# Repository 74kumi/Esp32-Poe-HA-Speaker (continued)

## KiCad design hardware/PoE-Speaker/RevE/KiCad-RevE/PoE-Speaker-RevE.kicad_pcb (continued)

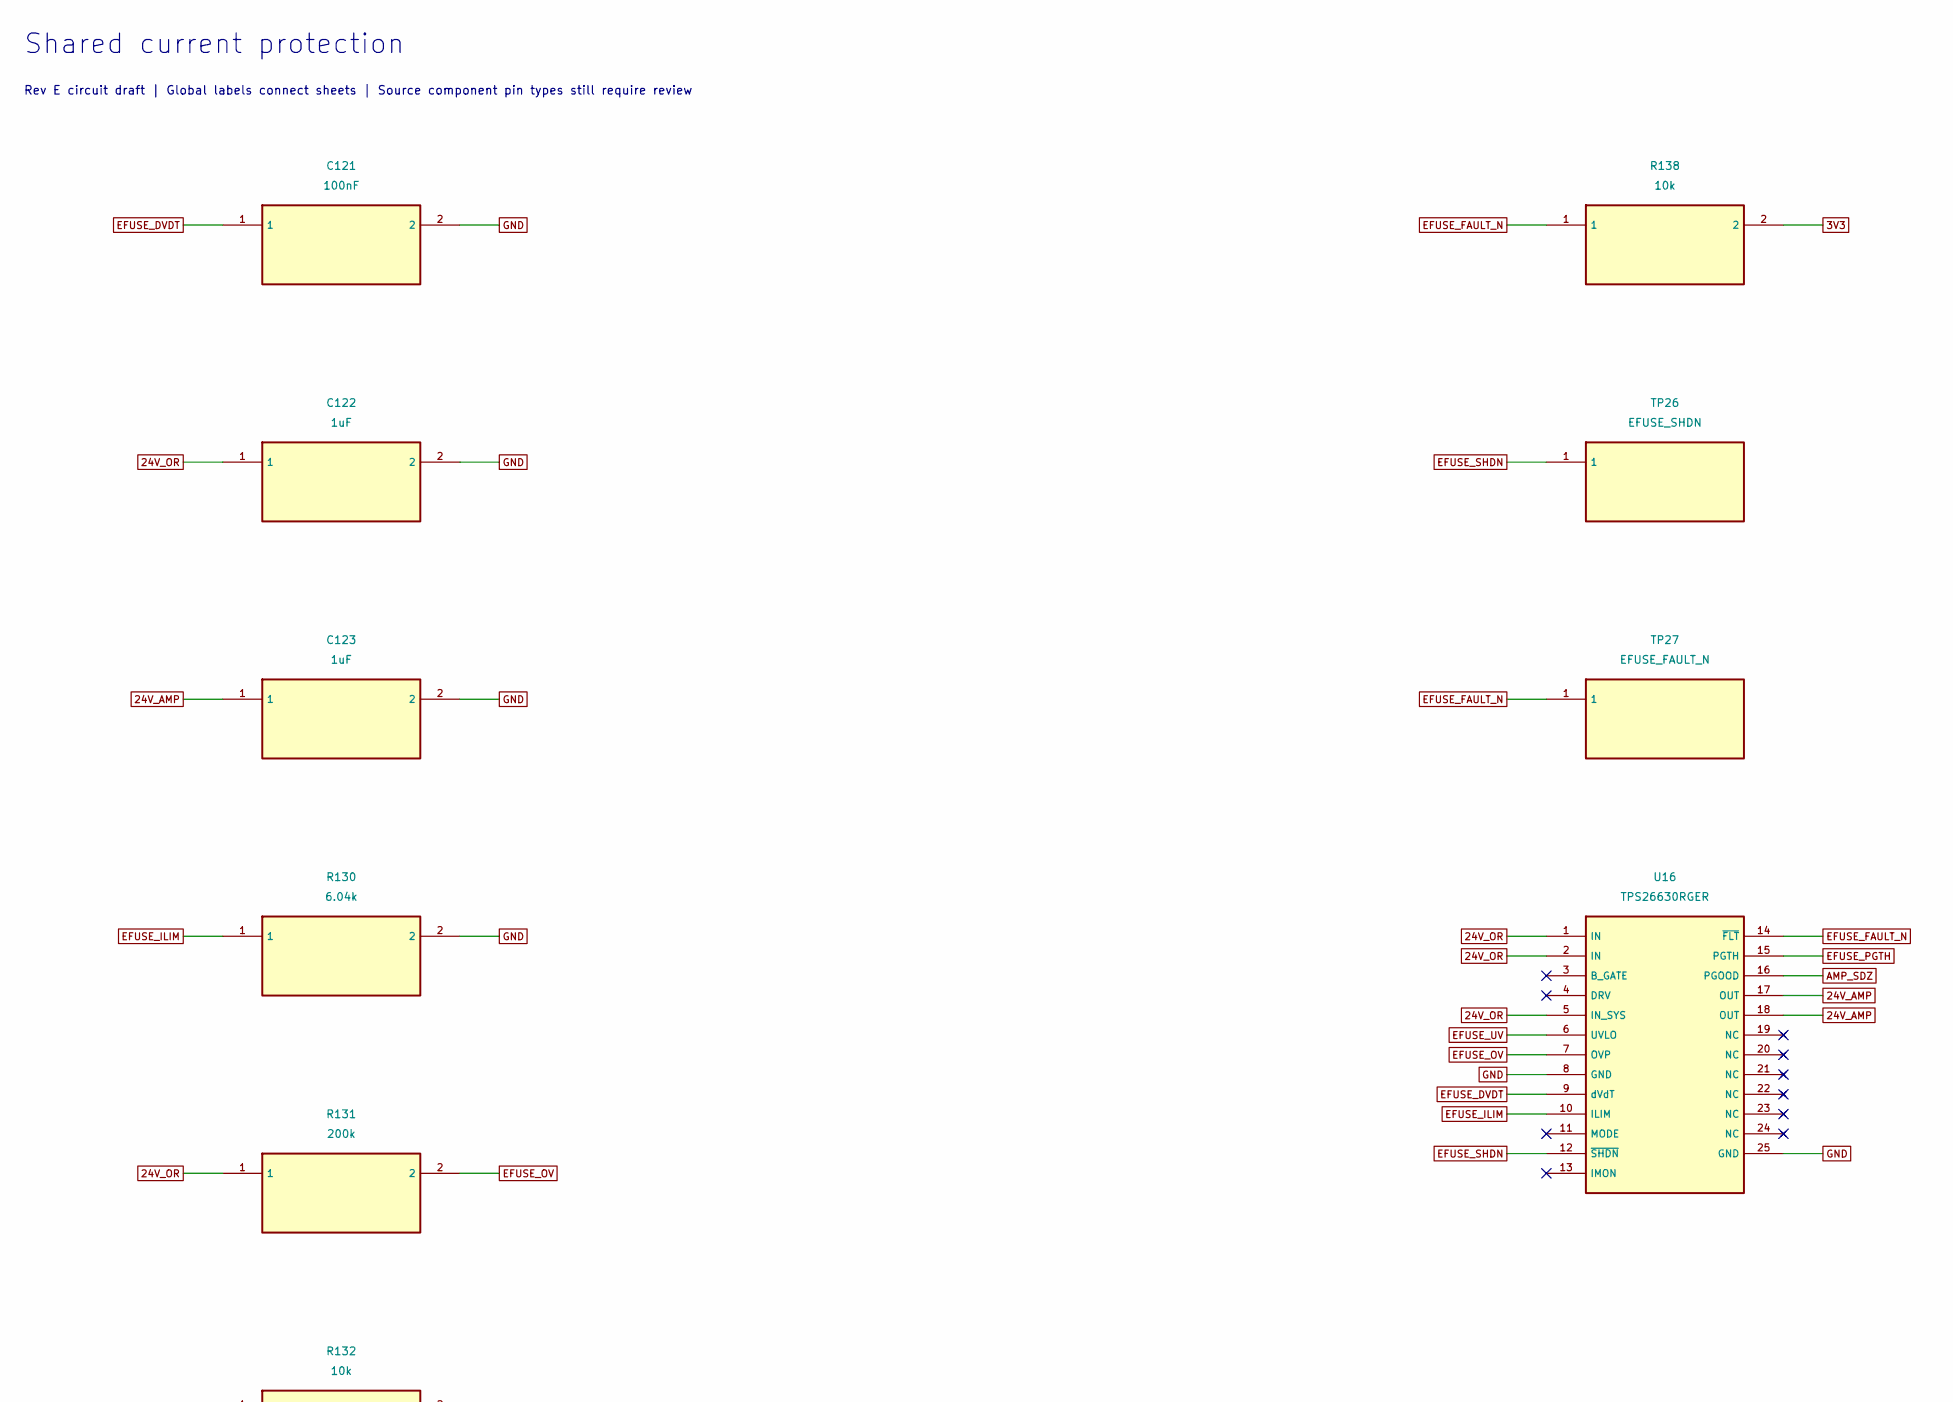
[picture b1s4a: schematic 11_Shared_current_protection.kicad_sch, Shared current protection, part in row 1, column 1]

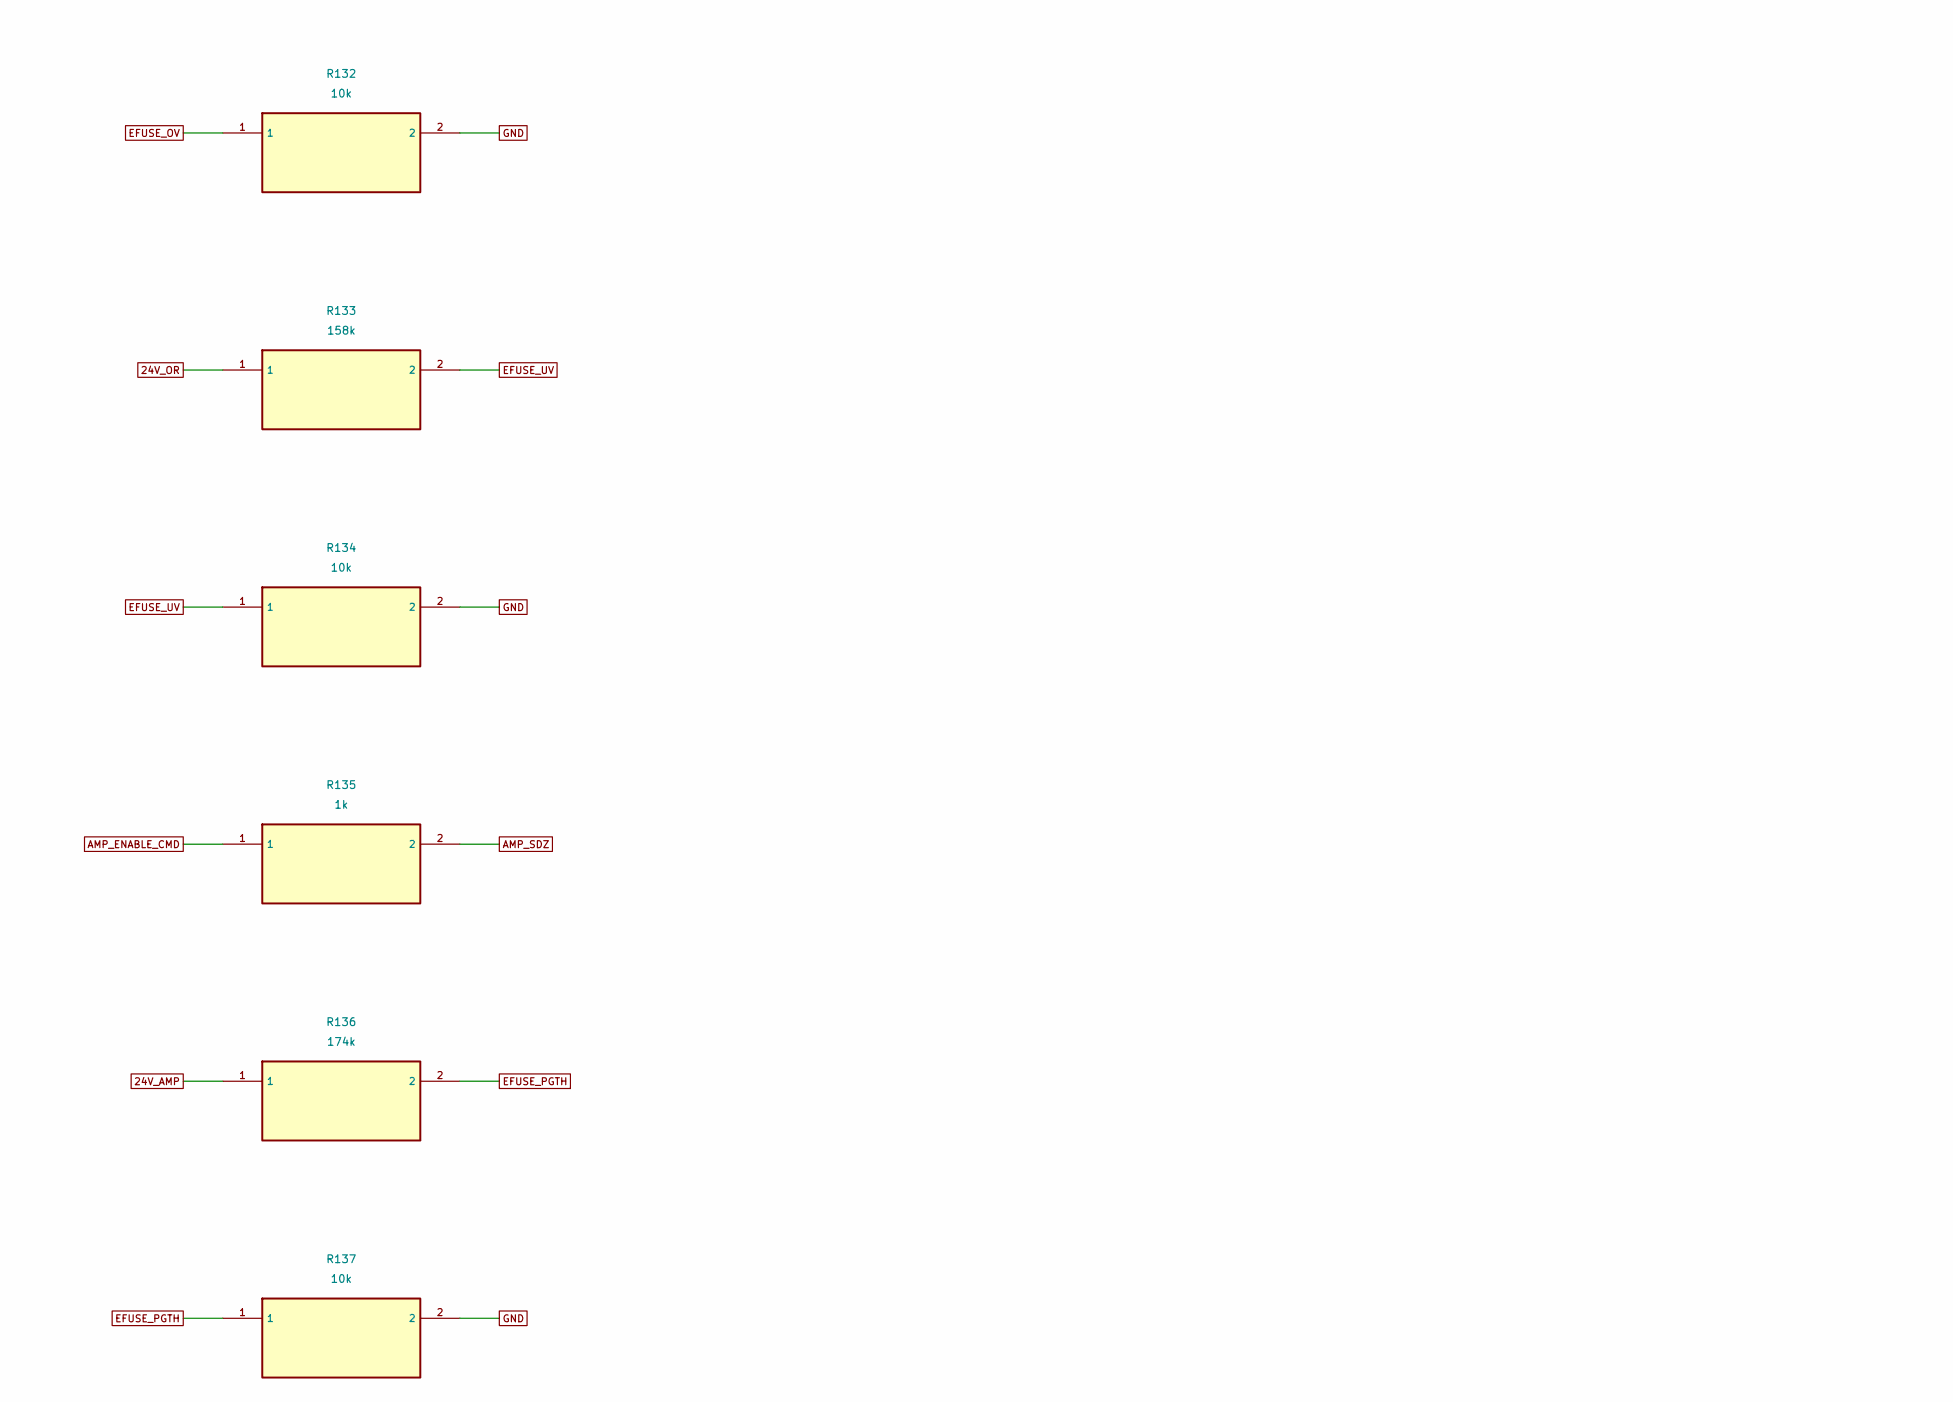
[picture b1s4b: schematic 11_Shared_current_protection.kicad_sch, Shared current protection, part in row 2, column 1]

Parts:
C121: 100nF; C_1210_3225Metric; Voltage Rating 100 V; Tolerance 5%; Manufacturer Part Number C1210C104J1GACTU
C122: 1uF; C_1210_3225Metric; Voltage Rating 100 V; Tolerance 10%; Manufacturer Part Number C1210C105K1RACTU
C123: 1uF; C123_RevB; Voltage Rating 50 V; Tolerance 10%; Manufacturer Part Number C0805C105K5RACTU
R130: 6.04k; R130_RevB; Tolerance 1%; Power rating 0.125 W conservative; Manufacturer Part Number TNPW08056K04FHEA
R131: 200k; R131_RevB; Tolerance 0.1%; Power rating 0.125 W conservative; Manufacturer Part Number TNPW0805200KBYEA
R132: 10k; R132_RevB; Tolerance 0.1%; Power rating 0.125 W conservative; Manufacturer Part Number TNPW080510K0BYEA
R133: 158k; R133_RevB; Tolerance 1%; Power rating 0.125 W conservative; Manufacturer Part Number TNPW0805158KFHEA
R134: 10k; R134_RevB; Tolerance 1%; Power rating 0.125 W conservative; Manufacturer Part Number TNPW080510K0FHEA
R135: 1k; R135_RevB; Tolerance 1%; Power rating 0.125 W conservative; Manufacturer Part Number TNPW08051K00FHEA
R136: 174k; R136_RevB; Tolerance 1%; Power rating 0.125 W conservative; Manufacturer Part Number TNPW0805174KFHEA
R137: 10k; R137_RevB; Tolerance 1%; Power rating 0.125 W conservative; Manufacturer Part Number TNPW080510K0FHEA
R138: 10k; R138_RevB; Tolerance 1%; Power rating 0.125 W conservative; Manufacturer Part Number TNPW080510K0FHEA
TP26: EFUSE_SHDN; TP26_RevB; Manufacturer Part Number TBD
TP27: EFUSE_FAULT_N; TP27_RevB; Manufacturer Part Number TBD
U16: TPS26630RGER; U16_RevB; Manufacturer Part Number TPS26630RGER

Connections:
3V3: R138.2; also elsewhere on the board
24V_AMP: C123.1, R136.1, U16.17 (OUT), U16.18 (OUT); also elsewhere on the board
24V_OR: C122.1, R131.1, R133.1, U16.1 (IN), U16.2 (IN), U16.5 (IN_SYS); also elsewhere on the board
AMP_ENABLE_CMD: R135.1; also elsewhere on the board
AMP_SDZ: R135.2, U16.16 (PGOOD); also elsewhere on the board
EFUSE_DVDT: C121.1, U16.9 (dVdT)
EFUSE_FAULT_N: R138.1, TP27.1, U16.14 (~FLT)
EFUSE_ILIM: R130.1, U16.10 (ILIM)
EFUSE_OV: R131.2, R132.1, U16.7 (OVP)
EFUSE_PGTH: R136.2, R137.1, U16.15 (PGTH)
EFUSE_SHDN: TP26.1, U16.12 (~SHDN)
EFUSE_UV: R133.2, R134.1, U16.6 (UVLO)
GND: C121.2, C122.2, C123.2, R130.2, R132.2, R134.2, R137.2, U16.8 (GND), U16.25 (GND); also elsewhere on the board

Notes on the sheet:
Rev E circuit draft | Global labels connect sheets | Source component pin types still require review
Shared current protection

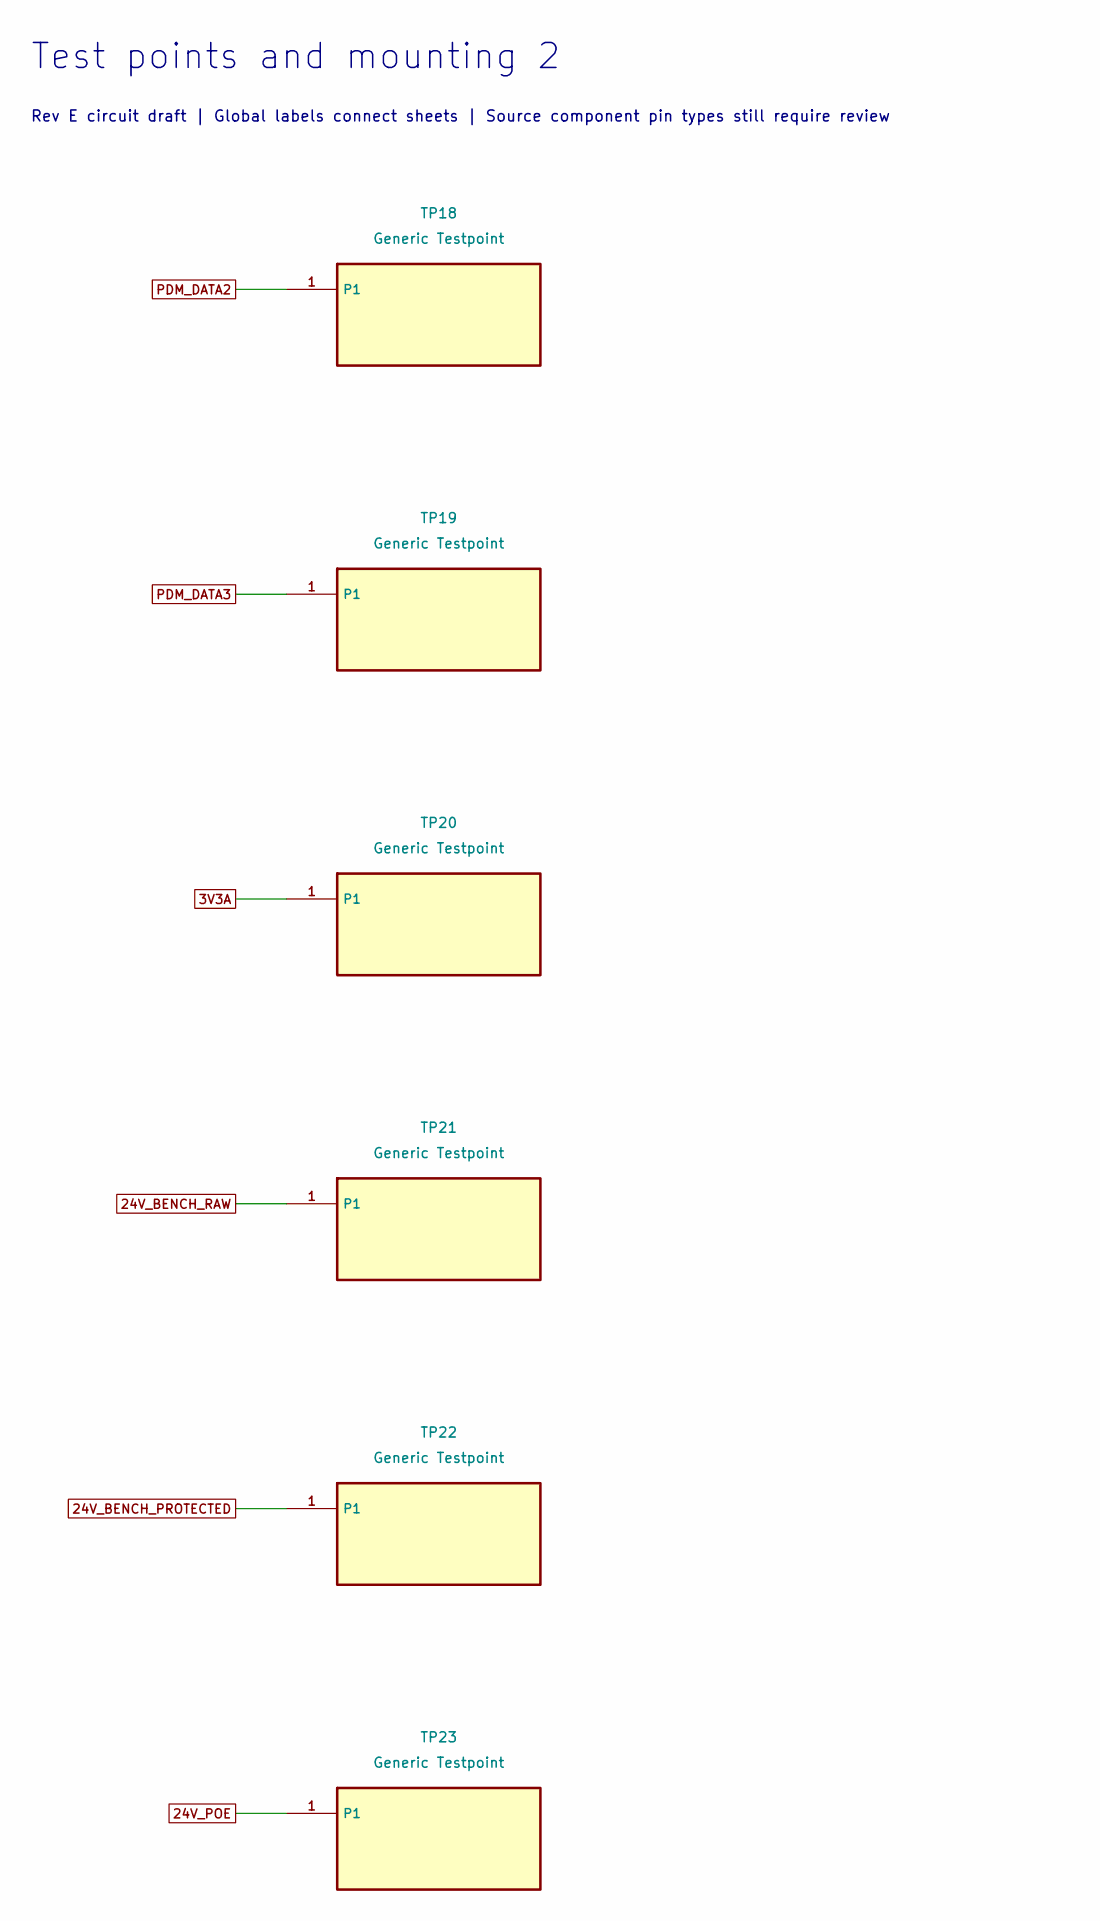
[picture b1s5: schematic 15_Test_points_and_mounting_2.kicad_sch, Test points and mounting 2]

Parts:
TP18: Generic Testpoint; TP18_RevB; Part Type Test Point
TP19: Generic Testpoint; TP19_RevB; Part Type Test Point
TP20: Generic Testpoint; TP20_RevB; Part Type Test Point
TP21: Generic Testpoint; TP21_RevB; Part Type Test Point
TP22: Generic Testpoint; TP22_RevB; Part Type Test Point
TP23: Generic Testpoint; TP23_RevB; Part Type Test Point

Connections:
3V3A: TP20.1; also elsewhere on the board
24V_BENCH_PROTECTED: TP22.1; also elsewhere on the board
24V_BENCH_RAW: TP21.1; also elsewhere on the board
24V_POE: TP23.1; also elsewhere on the board
PDM_DATA2: TP18.1; also elsewhere on the board
PDM_DATA3: TP19.1; also elsewhere on the board

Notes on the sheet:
Test points and mounting 2
Rev E circuit draft | Global labels connect sheets | Source component pin types still require review

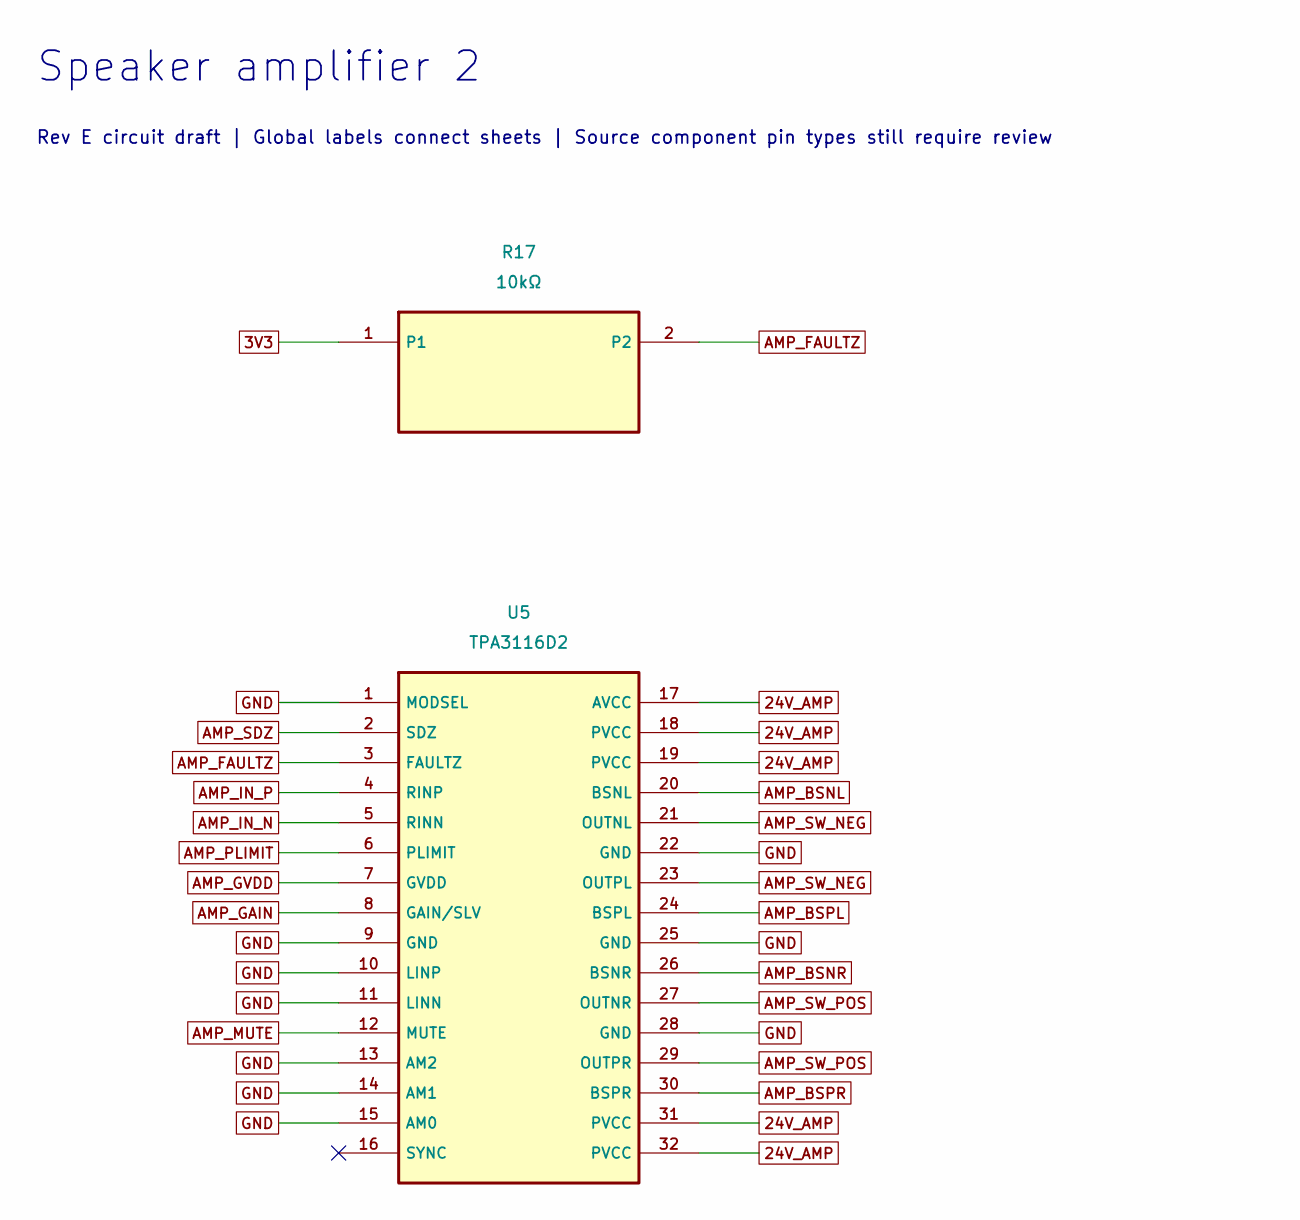
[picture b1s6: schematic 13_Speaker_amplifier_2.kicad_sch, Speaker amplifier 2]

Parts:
R17: 10kΩ; R17_RevB; Tolerance 1%; Power rating 0.10 W conservative; Part Type Resistor
U5: TPA3116D2; U5_RevB; Part Type Integrated Circuit

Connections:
3V3: R17.1; also elsewhere on the board
24V_AMP: U5.17 (AVCC), U5.18 (PVCC), U5.19 (PVCC), U5.31 (PVCC), U5.32 (PVCC); also elsewhere on the board
AMP_BSNL: U5.20 (BSNL); also elsewhere on the board
AMP_BSNR: U5.26 (BSNR); also elsewhere on the board
AMP_BSPL: U5.24 (BSPL); also elsewhere on the board
AMP_BSPR: U5.30 (BSPR); also elsewhere on the board
AMP_FAULTZ: R17.2, U5.3 (FAULTZ); also elsewhere on the board
AMP_GAIN: U5.8 (GAIN/SLV); also elsewhere on the board
AMP_GVDD: U5.7 (GVDD); also elsewhere on the board
AMP_IN_N: U5.5 (RINN); also elsewhere on the board
AMP_IN_P: U5.4 (RINP); also elsewhere on the board
AMP_MUTE: U5.12 (MUTE); also elsewhere on the board
AMP_PLIMIT: U5.6 (PLIMIT); also elsewhere on the board
AMP_SDZ: U5.2 (SDZ); also elsewhere on the board
AMP_SW_NEG: U5.21 (OUTNL), U5.23 (OUTPL); also elsewhere on the board
AMP_SW_POS: U5.27 (OUTNR), U5.29 (OUTPR); also elsewhere on the board
GND: U5.1 (MODSEL), U5.9 (GND), U5.10 (LINP), U5.11 (LINN), U5.13 (AM2), U5.14 (AM1), U5.15 (AM0), U5.22 (GND), U5.25 (GND), U5.28 (GND); also elsewhere on the board

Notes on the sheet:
Speaker amplifier 2
Rev E circuit draft | Global labels connect sheets | Source component pin types still require review

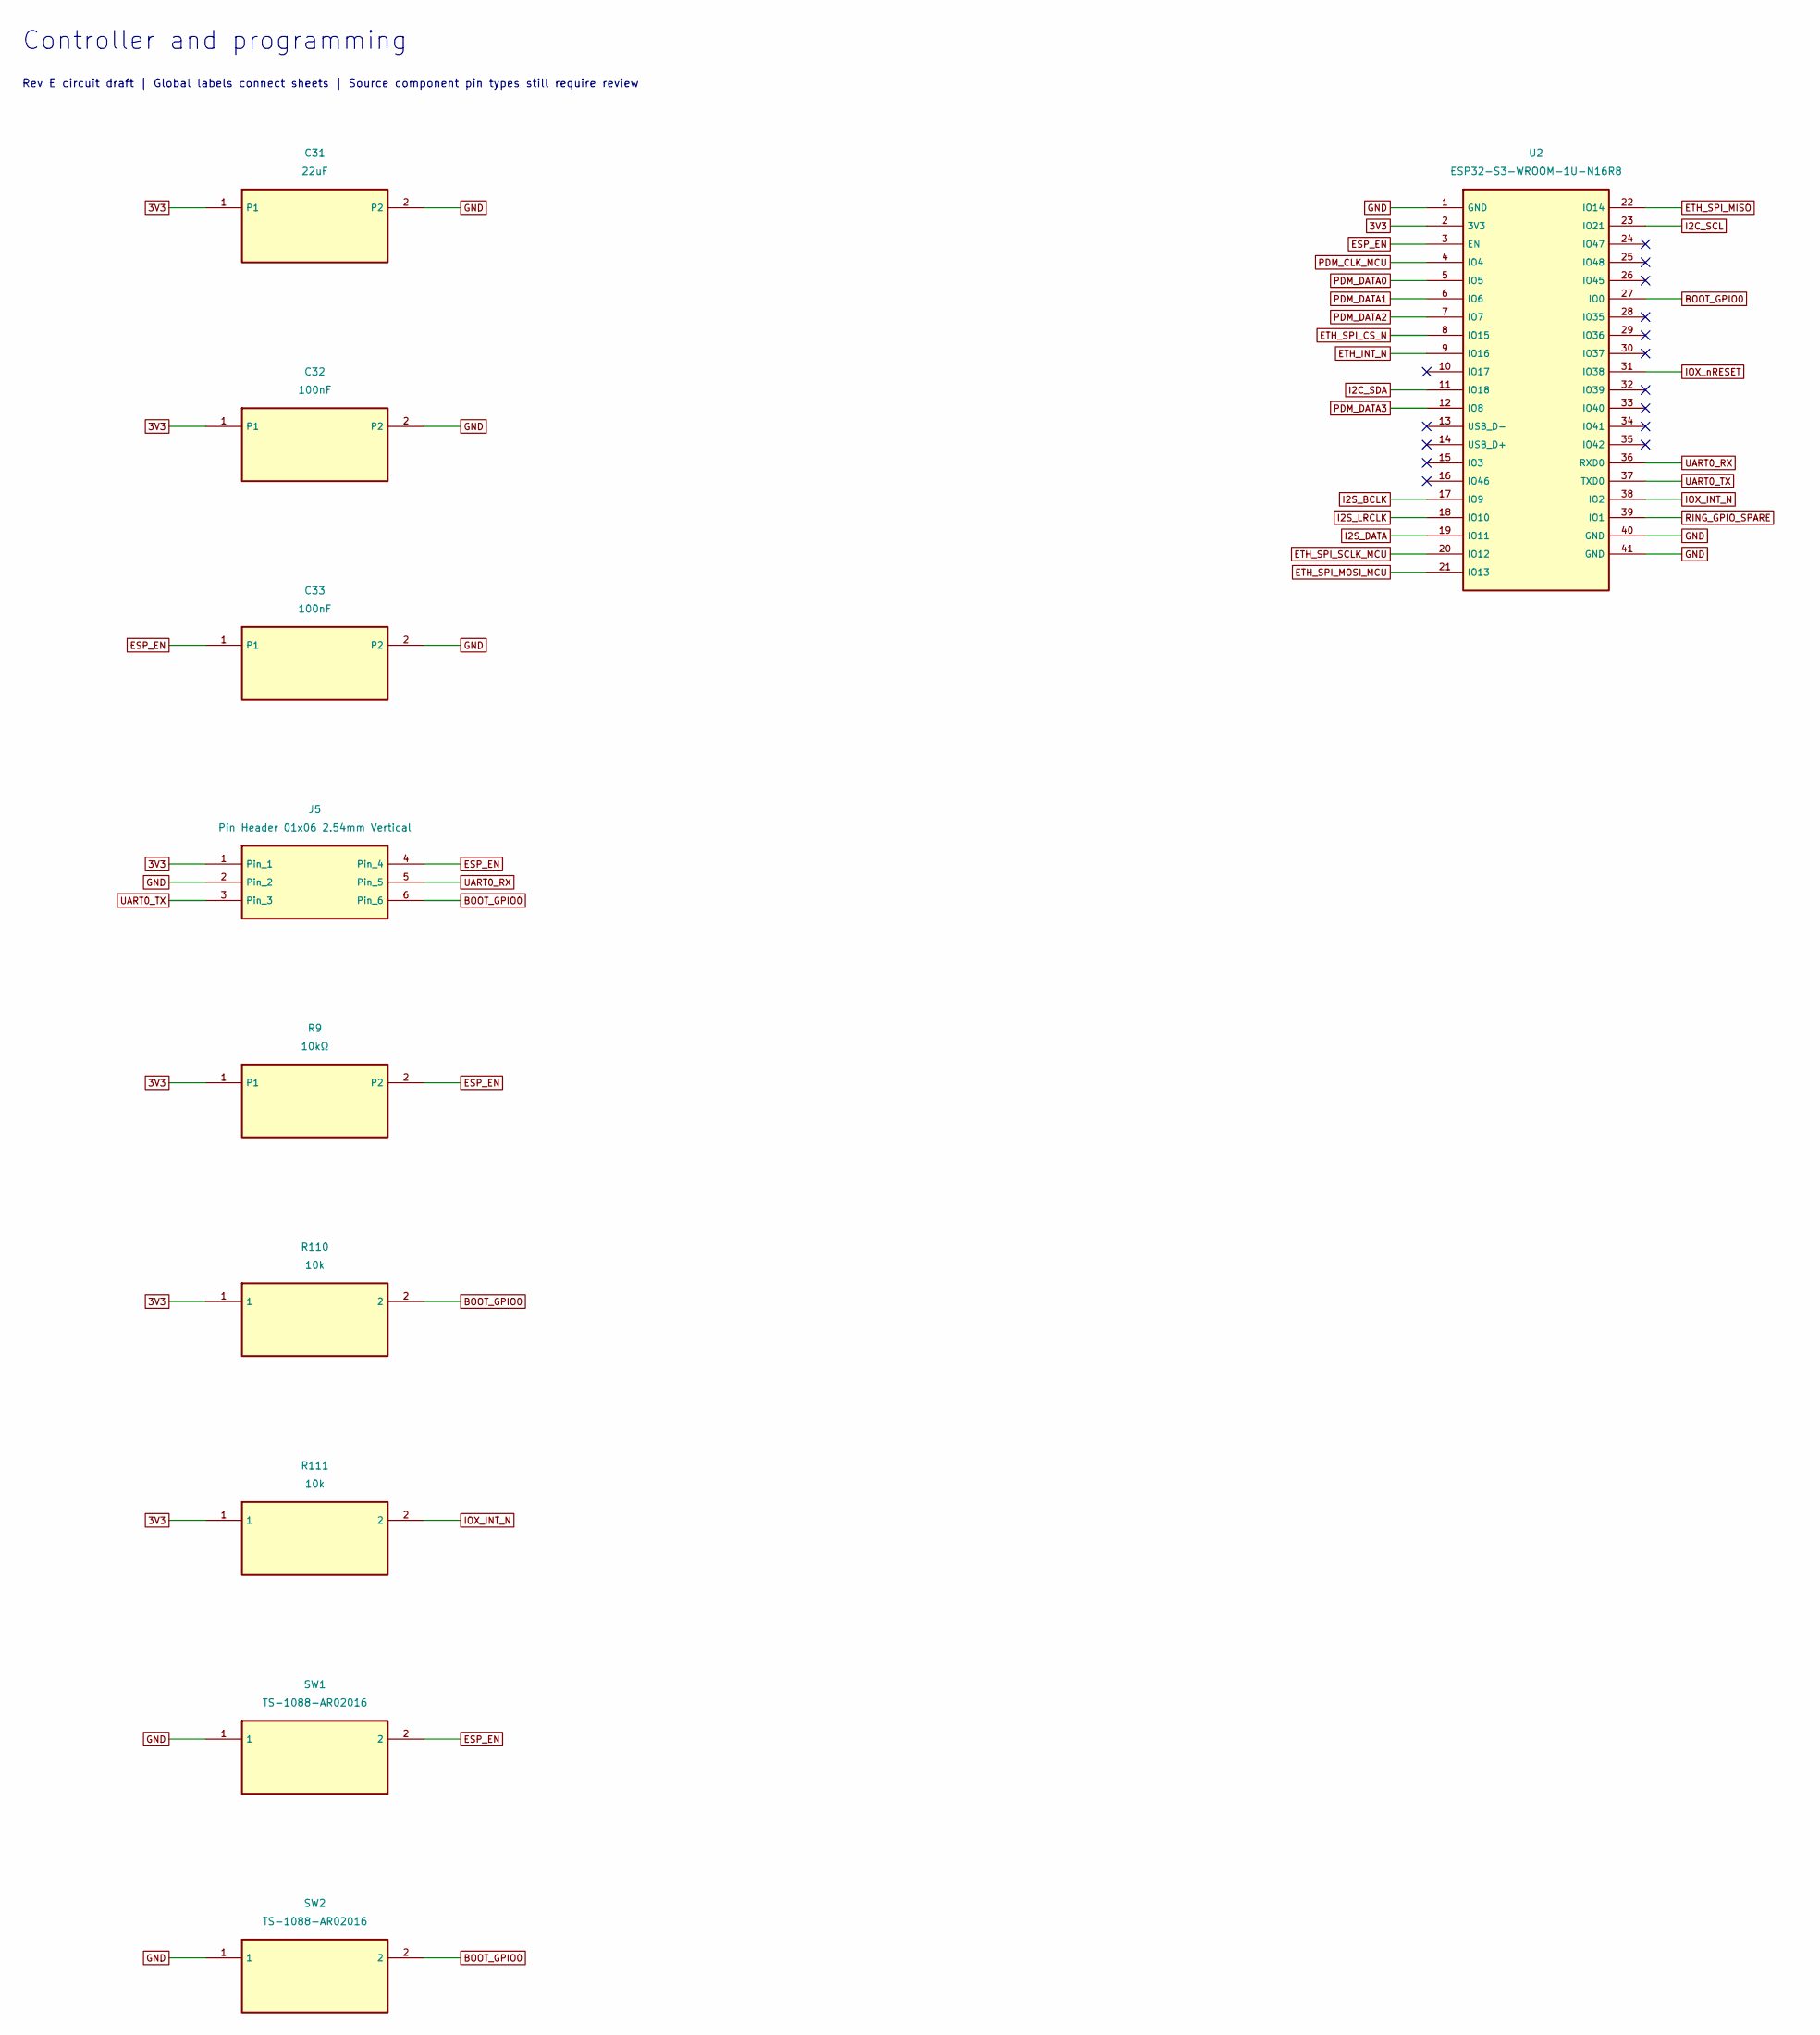
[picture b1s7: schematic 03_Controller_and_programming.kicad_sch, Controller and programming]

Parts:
C31: 22uF; C31_RevB; Voltage Rating 16 V; Tolerance 20%; Manufacturer Part Number GRM21BR61C226ME44L
C32: 100nF; C32_RevB; Voltage Rating 50 V; Tolerance 10%; Manufacturer Part Number C0603C104K5RACTU
C33: 100nF; C33_RevB; Voltage Rating 50 V; Tolerance 10%; Manufacturer Part Number C0603C104K5RACTU
J5: Pin Header 01x06 2.54mm Vertical; J5_RevB; Part Type Connector
R9: 10kΩ; R9_RevB; Tolerance 1%; Power rating 0.10 W conservative; Part Type Resistor
R110: 10k; R110_RevB; Tolerance 1%; Power rating 0.10 W conservative; Manufacturer Part Number TNPW060310K0FHEA
R111: 10k; R111_RevB; Tolerance 1%; Power rating 0.10 W conservative; Manufacturer Part Number TNPW060310K0FHEA
SW1: TS-1088-AR02016; SW1_RevB; Manufacturer Part Number TS-1088-AR02016; JLCPCB Part Class Extended Part
SW2: TS-1088-AR02016; SW2_RevB; Manufacturer Part Number TS-1088-AR02016; JLCPCB Part Class Extended Part
U2: ESP32-S3-WROOM-1U-N16R8; U2_RevB; Manufacturer Part Number ESP32-S3-WROOM-1U-N16R8

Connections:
3V3: C31.1, C32.1, J5.1, R9.1, R110.1, R111.1, U2.2 (3V3); also elsewhere on the board
BOOT_GPIO0: J5.6, R110.2, SW2.2, U2.27 (IO0)
ESP_EN: C33.1, J5.4, R9.2, SW1.2, U2.3 (EN)
ETH_INT_N: U2.9 (IO16); also elsewhere on the board
ETH_SPI_CS_N: U2.8 (IO15); also elsewhere on the board
ETH_SPI_MISO: U2.22 (IO14); also elsewhere on the board
ETH_SPI_MOSI_MCU: U2.21 (IO13); also elsewhere on the board
ETH_SPI_SCLK_MCU: U2.20 (IO12); also elsewhere on the board
GND: C31.2, C32.2, C33.2, J5.2, SW1.1, SW2.1, U2.1 (GND), U2.40 (GND), U2.41 (GND); also elsewhere on the board
I2C_SCL: U2.23 (IO21); also elsewhere on the board
I2C_SDA: U2.11 (IO18); also elsewhere on the board
I2S_BCLK: U2.17 (IO9); also elsewhere on the board
I2S_DATA: U2.19 (IO11); also elsewhere on the board
I2S_LRCLK: U2.18 (IO10); also elsewhere on the board
IOX_INT_N: R111.2, U2.38 (IO2); also elsewhere on the board
IOX_nRESET: U2.31 (IO38); also elsewhere on the board
PDM_CLK_MCU: U2.4 (IO4); also elsewhere on the board
PDM_DATA0: U2.5 (IO5); also elsewhere on the board
PDM_DATA1: U2.6 (IO6); also elsewhere on the board
PDM_DATA2: U2.7 (IO7); also elsewhere on the board
PDM_DATA3: U2.12 (IO8); also elsewhere on the board
RING_GPIO_SPARE: U2.39 (IO1); also elsewhere on the board
UART0_RX: J5.5, U2.36 (RXD0)
UART0_TX: J5.3, U2.37 (TXD0)

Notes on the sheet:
Rev E circuit draft | Global labels connect sheets | Source component pin types still require review
Controller and programming
